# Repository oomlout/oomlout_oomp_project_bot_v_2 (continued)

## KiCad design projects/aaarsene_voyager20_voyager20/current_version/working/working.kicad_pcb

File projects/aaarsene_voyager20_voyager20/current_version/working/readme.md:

# voyager20
 
## summary 
* id: aaarsene_voyager20_voyager20
* user: aaarsene
* name: voyager20
* board: voyager20
* repo: https://github.com/aaarsene/Voyager20
* src_file_repo_kicad_pcb: Voyager20.kicad_pcb
* src_file_repo_kicad_pcb_link: https://github.com/aaarsene/Voyager20/tree/FnRow/Voyager20.kicad_pcb

* src_file_repo_sch: 
* src_file_repo_sch_link: https://github.com/aaarsene/Voyager20/tree/FnRow/
* full details link: https://github.com/oomlout/oomlout_oomp_project_bot_v_2/tree/main/projects/aaarsene_voyager20_voyager20/current_version/working  

## schematic  
  
[schematic (pdf)](working_schematic.pdf) 

## pcb  

[board (pdf)](working.pdf)  

## working_bom
| Id | Designator | Footprint | Quantity | Designation | Supplier and ref |  | None | 
| --- | --- | --- | --- | --- | --- | --- | --- | 
| 1 | MX1,MX2,MX3,MX4,MX5,MX6,MX7,MX8,MX9,MX10,MX11,MX12,MX13,MX14,MX15,MX16,MX17,MX18,MX19,MX20,MX21,MX22,MX23,MX24 | MX-1U | 24 | MX-1U |  |  | [''] | 
| 2 | USB1 | HRO-TYPE-C-31-M-12-Assembly | 1 | HRO-TYPE-C-31-M-12 |  |  | [''] | 
| 3 | MX-E-1,MX-E-2,MX-E-3 | MX-2U-ReversedStabilizers | 3 | MX-2U |  |  | [''] | 
| 4 | G*** | ai-ring-6mm | 1 | LOGO |  |  | [''] | 
| 5 | C1,C2 | C_0603_1608Metric | 2 | 22p |  |  | [''] | 
| 6 | C3 | C_0603_1608Metric | 1 | 1uF |  |  | [''] | 
| 7 | C4,C5,CR1,CR2,CR3,CR4 | C_0603_1608Metric | 6 | 0.1u |  |  | [''] | 
| 8 | C6 | C_0603_1608Metric | 1 | 4.7u |  |  | [''] | 
| 9 | D1,D2,D3,D4,D5,D6,D10,D11,D12,D13,D16,D17,D19,D20,D21,D22,D15,D14,D8,D7,D25,D26,D27,D28 | D_SOD-123 | 24 | SOD-123 |  |  | [''] | 
| 10 | D9,D23,D24,D18 | LED_WS2812B_PLCC4_5.0x5.0mm_P3.2mm | 4 | WS2812B |  |  | [''] | 
| 11 | F1 | Fuse_1206_3216Metric | 1 | 500mA |  |  | [''] | 
| 12 | R1,R5 | R_0805_2012Metric | 2 | 10k |  |  | [''] | 
| 13 | R2,R3 | R_0805_2012Metric | 2 | 22 |  |  | [''] | 
| 14 | R4,R6 | R_0805_2012Metric | 2 | 5.1k |  |  | [''] | 
| 15 | R7,R10,R11,R12,R13,R14,R15,R16,R17,R18,R21,R22,R23,R24,R25,R26,R27,R20,R19,R9,R8,R28,R29,R30,R31 | R_0805_2012Metric | 25 | 1k |  |  | [''] | 
| 16 | SW1 | SKQG-1155865 | 1 | SW_Push |  |  | [''] | 
| 17 | Y1 | Crystal_SMD_3225-4Pin_3.2x2.5mm | 1 | 16MHz |  |  | [''] | 
| 18 | U1 | QFN-32-1EP_5x5mm_P0.5mm_EP3.65x3.65mm | 1 | ATmega32U2-AU |  |  | [''] | 
| 19 | Q1 | SOT-23 | 1 | Q_NPN_BEC |  |  | [''] | 
| 20 | U2 | SOT143B | 1 | PRTR5V0U2X |  |  | [''] | 

## bom_schematic
| Ref | Qnty | Value | Cmp name | Footprint | Description | Vendor | DNP | 
| --- | --- | --- | --- | --- | --- | --- | --- | 
| C1, C2 | 2 | 22p | C_Small | Capacitor_SMD:C_0603_1608Metric | Unpolarized capacitor, small symbol |  |  | 
| C3 | 1 | 1uF | C_Small | Capacitor_SMD:C_0603_1608Metric | Unpolarized capacitor, small symbol |  |  | 
| C4, C5 | 2 | 0.1u | C_Small | Capacitor_SMD:C_0603_1608Metric | Unpolarized capacitor, small symbol |  |  | 
| C6 | 1 | 4.7u | C_Small | Capacitor_SMD:C_0603_1608Metric | Unpolarized capacitor, small symbol |  |  | 
| CR1, CR2, CR3, CR4 | 4 | 0.1u | C_Small | Capacitor_SMD:C_0603_1608Metric | Unpolarized capacitor, small symbol |  |  | 
| D1, D2, D3, D4, D5, D6, D7, D8, D10, D11, D12, D13, D14, D15, D16, D17, D19, D20, D21, D22, D25, D26, D27, D28 | 24 | SOD-123 | D_Small | Diode_SMD:D_SOD-123 | Diode, small symbol |  |  | 
| D9, D18, D23, D24 | 4 | WS2812B | WS2812B | LED_SMD:LED_WS2812B_PLCC4_5.0x5.0mm_P3.2mm | RGB LED with integrated controller |  |  | 
| F1 | 1 | 500mA | Polyfuse_Small | Fuse:Fuse_1206_3216Metric | Resettable fuse, polymeric positive temperature coefficient, small symbol |  |  | 
| MX1, MX2, MX3, MX4, MX5, MX6, MX7, MX8, MX9, MX10, MX11, MX12, MX13, MX14, MX15, MX16, MX17, MX18, MX19, MX20, MX21, MX22, MX23, MX24 | 24 | MX-1U | MX-1U-MX_Alps_Hybrids | MX_Alps_Hybrid:MX-1U |  |  |  | 
| MX-E-1, MX-E-2, MX-E-3 | 3 | MX-2U | MX-1U-MX_Alps_Hybrids | MX_Alps_Hybrid:MX-2U-ReversedStabilizers |  |  |  | 
| Q1 | 1 | Q_NPN_BEC | Q_NPN_BEC | Package_TO_SOT_SMD:SOT-23 | NPN transistor, base/emitter/collector |  |  | 
| R1, R5 | 2 | 10k | R_Small | Resistor_SMD:R_0805_2012Metric | Resistor, small symbol |  |  | 
| R2, R3 | 2 | 22 | R_Small | Resistor_SMD:R_0805_2012Metric | Resistor, small symbol |  |  | 
| R4, R6 | 2 | 5.1k | R_Small | Resistor_SMD:R_0805_2012Metric | Resistor, small symbol |  |  | 
| R7, R8, R9, R10, R11, R12, R13, R14, R15, R16, R17, R18, R19, R20, R21, R22, R23, R24, R25, R26, R27, R28, R29, R30, R31 | 25 | 1k | R_Small | Resistor_SMD:R_0805_2012Metric | Resistor, small symbol |  |  | 
| SW1 | 1 | SW_Push | SW_Push | random-keyboard-parts:SKQG-1155865 | Push button switch, generic, two pins |  |  | 
| U1 | 1 | ATmega32U2-AU | ATmega32U2-AU-MCU_Microchip_ATmega | Package_DFN_QFN:QFN-32-1EP_5x5mm_P0.5mm_EP3.65x3.65mm |  |  |  | 
| U2 | 1 | PRTR5V0U2X | PRTR5V0U2X | random-keyboard-parts:SOT143B |  |  |  | 
| USB1 | 1 | HRO-TYPE-C-31-M-12 | HRO-TYPE-C-31-M-12-Type-C | Type-C:HRO-TYPE-C-31-M-12-Assembly |  |  |  | 
| Y1 | 1 | 16MHz | Crystal_GND24_Small-Device | Crystal:Crystal_SMD_3225-4Pin_3.2x2.5mm |  |  |  |

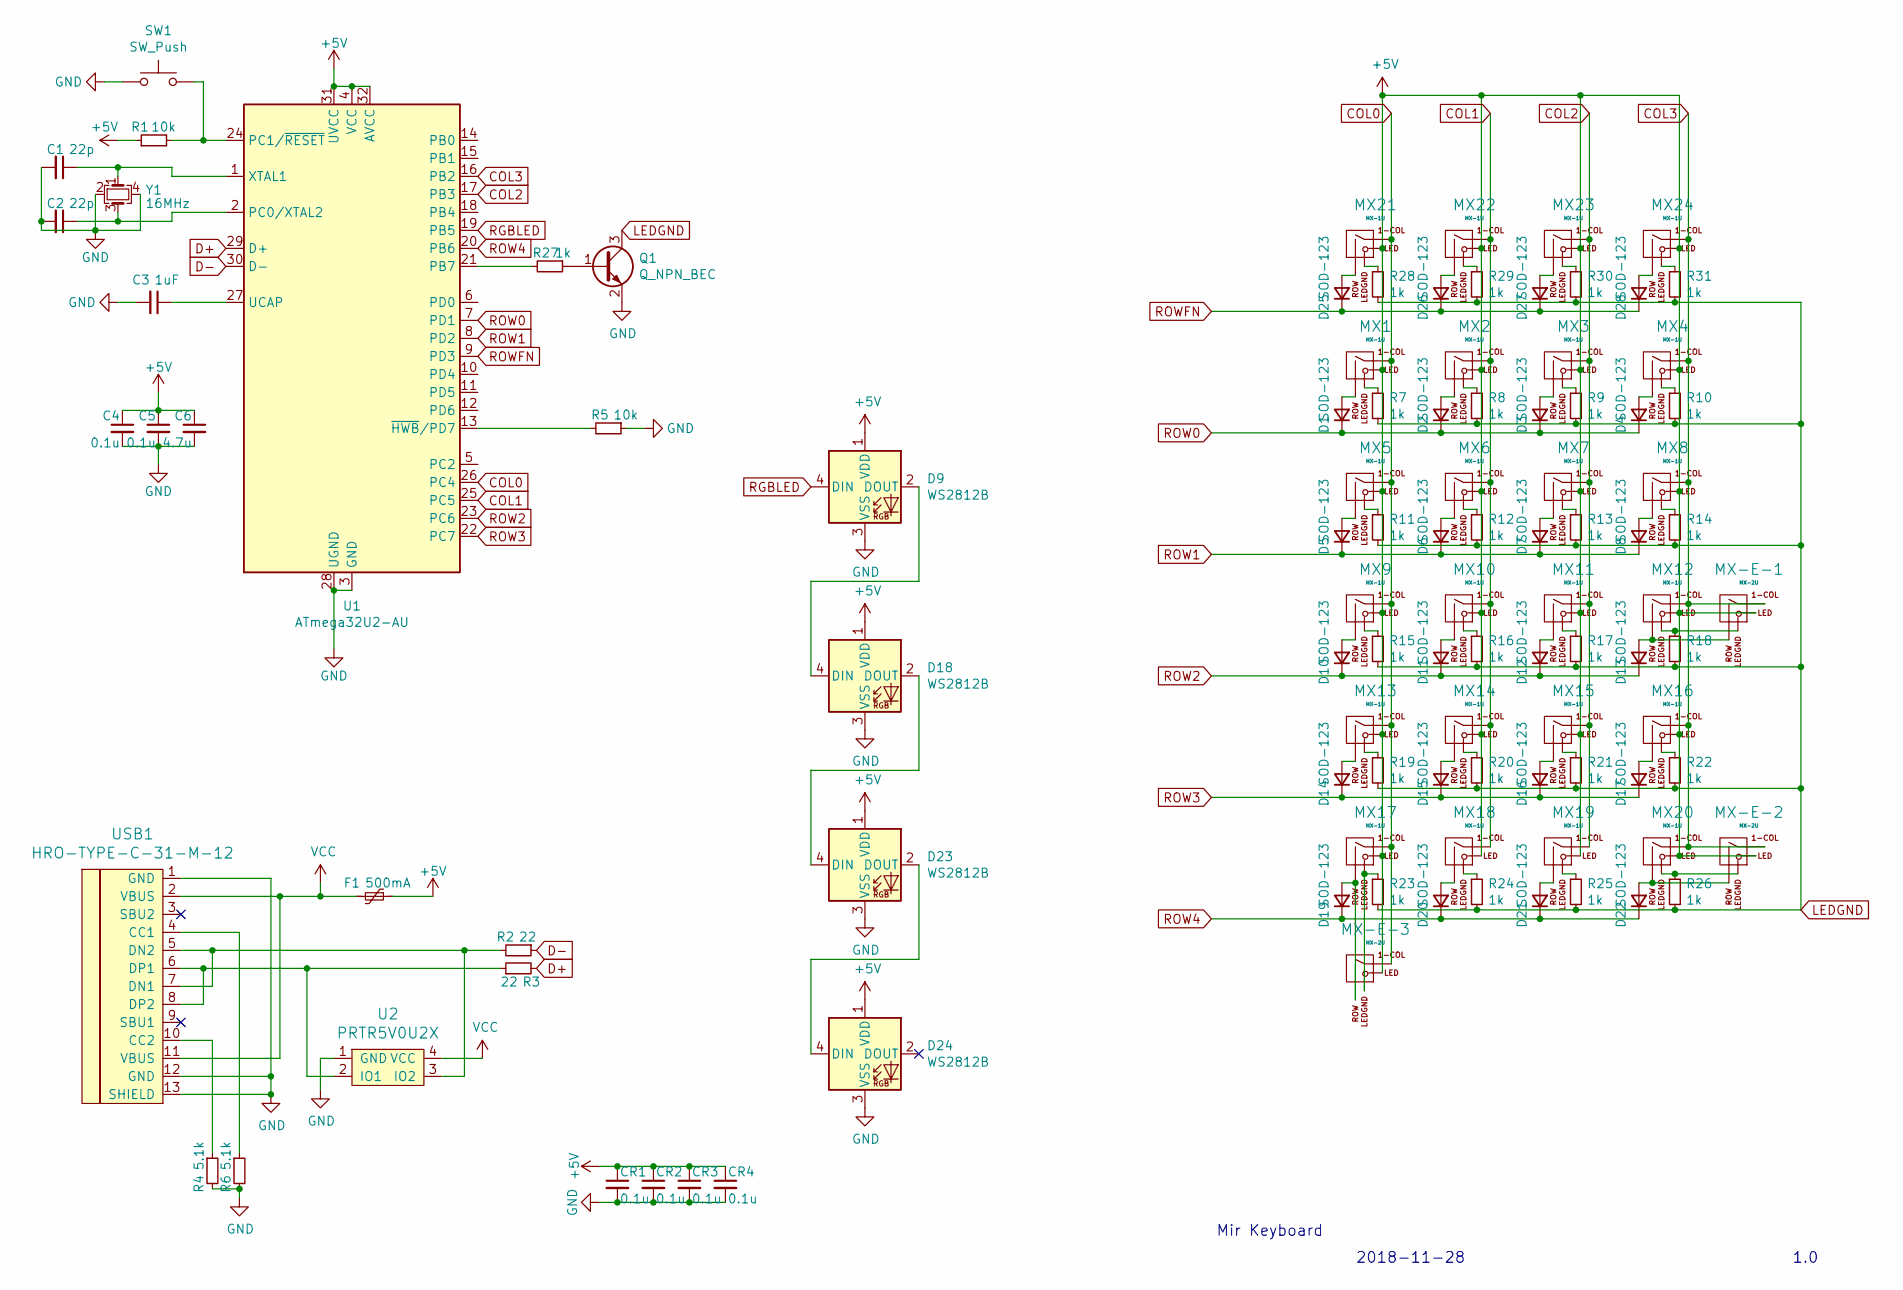
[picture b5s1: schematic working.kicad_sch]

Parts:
C1, C2: 22p; C_0603_1608Metric
C3: 1uF; C_0603_1608Metric
C4, C5: 0.1u; C_0603_1608Metric
C6: 4.7u; C_0603_1608Metric
CR1, CR2, CR3, CR4: 0.1u; C_0603_1608Metric
D1, D2, D3, D4, D5, D6, D7, D8, D10, D11, D12, D13, D14, D15, D16, D17, D19, D20, D21, D22, D25, D26, D27, D28: SOD-123; D_SOD-123
D9, D18, D23, D24: WS2812B; LED_WS2812B_PLCC4_5.0x5.0mm_P3.2mm
F1: 500mA; Fuse_1206_3216Metric
MX1, MX2, MX3, MX4, MX5, MX6, MX7, MX8, MX9, MX10, MX11, MX12, MX13, MX14, MX15, MX16, MX17, MX18, MX19, MX20, MX21, MX22, MX23, MX24: MX-1U
MX-E-1, MX-E-2, MX-E-3: MX-2U; MX-2U-ReversedStabilizers
Q1: Q_NPN_BEC; SOT-23
R1, R5: 10k; R_0805_2012Metric
R2, R3: 22; R_0805_2012Metric
R4, R6: 5.1k; R_0805_2012Metric
R7, R8, R9, R10, R11, R12, R13, R14, R15, R16, R17, R18, R19, R20, R21, R22, R23, R24, R25, R26, R27, R28, R29, R30, R31: 1k; R_0805_2012Metric
SW1: SW_Push; SKQG-1155865
U1: ATmega32U2-AU; QFN-32-1EP_5x5mm_P0.5mm_EP3.65x3.65mm
U2: PRTR5V0U2X; SOT143B
USB1: HRO-TYPE-C-31-M-12; HRO-TYPE-C-31-M-12-Assembly
Y1: 16MHz; Crystal_SMD_3225-4Pin_3.2x2.5mm

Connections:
+5V: C4.1, C5.1, C6.1, CR1.1, CR2.1, CR3.1, CR4.1, D9.1 (VDD), D18.1 (VDD), D23.1 (VDD), D24.1 (VDD), F1.1, MX1.3 (LED), MX2.3 (LED), MX3.3 (LED), MX4.3 (LED), MX5.3 (LED), MX6.3 (LED), MX7.3 (LED), MX8.3 (LED), MX9.3 (LED), MX10.3 (LED), MX11.3 (LED), MX12.3 (LED), MX13.3 (LED), MX14.3 (LED), MX15.3 (LED), MX16.3 (LED), MX17.3 (LED), MX18.3 (LED), MX19.3 (LED), MX20.3 (LED), MX21.3 (LED), MX22.3 (LED), MX23.3 (LED), MX24.3 (LED), MX-E-1.3 (LED), MX-E-2.3 (LED), MX-E-3.3 (LED), R1.1, U1.4 (VCC), U1.31 (UVCC), U1.32 (AVCC)
COL0: MX1.1 (COL), MX5.1 (COL), MX9.1 (COL), MX13.1 (COL), MX17.1 (COL), MX21.1 (COL), MX-E-3.1 (COL), U1.26 (PC4)
COL1: MX2.1 (COL), MX6.1 (COL), MX10.1 (COL), MX14.1 (COL), MX18.1 (COL), MX22.1 (COL), U1.25 (PC5)
COL2: MX3.1 (COL), MX7.1 (COL), MX11.1 (COL), MX15.1 (COL), MX19.1 (COL), MX23.1 (COL), U1.17 (PB3)
COL3: MX4.1 (COL), MX8.1 (COL), MX12.1 (COL), MX16.1 (COL), MX20.1 (COL), MX24.1 (COL), MX-E-1.1 (COL), MX-E-2.1 (COL), U1.16 (PB2)
D+: R3.2, U1.29 (D+)
D-: R2.1, U1.30 (D-)
GND: C1.2, C2.2, C3.2, C4.2, C5.2, C6.2, CR1.2, CR2.2, CR3.2, CR4.2, D9.3 (VSS), D18.3 (VSS), D23.3 (VSS), D24.3 (VSS), Q1.2 (E), R4.2, R5.1, R6.2, SW1.1, U1.3 (GND), U1.28 (UGND), U2.1 (GND), USB1.1 (GND), USB1.12 (GND), USB1.13 (SHIELD), Y1.2, Y1.4
LEDGND: Q1.3 (C), R7.2, R8.2, R9.2, R10.2, R11.2, R12.2, R13.2, R14.2, R15.2, R16.2, R17.2, R18.2, R19.2, R20.2, R21.2, R22.2, R23.2, R24.2, R25.2, R26.2, R28.2, R29.2, R30.2, R31.2
unnamed: C1.1, U1.1 (XTAL1), Y1.1
unnamed: C2.1, U1.2 (PC0/XTAL2), Y1.3
unnamed: C3.1, U1.27 (UCAP)
unnamed: D1.2 (A), MX1.2 (ROW)
unnamed: D2.2 (A), MX2.2 (ROW)
unnamed: D3.2 (A), MX3.2 (ROW)
unnamed: D4.2 (A), MX4.2 (ROW)
unnamed: D5.2 (A), MX5.2 (ROW)
unnamed: D6.2 (A), MX6.2 (ROW)
unnamed: D7.2 (A), MX7.2 (ROW)
unnamed: D8.2 (A), MX8.2 (ROW)
unnamed: D10.2 (A), MX9.2 (ROW)
unnamed: D11.2 (A), MX10.2 (ROW)
unnamed: D12.2 (A), MX11.2 (ROW)
unnamed: D13.2 (A), MX12.2 (ROW), MX-E-1.2 (ROW)
unnamed: D14.2 (A), MX13.2 (ROW)
unnamed: D15.2 (A), MX14.2 (ROW)
unnamed: D16.2 (A), MX15.2 (ROW)
unnamed: D17.2 (A), MX16.2 (ROW)
unnamed: D18.2 (DOUT), D23.4 (DIN)
unnamed: D9.2 (DOUT), D18.4 (DIN)
unnamed: D19.2 (A), MX17.2 (ROW), MX-E-3.2 (ROW)
unnamed: D20.2 (A), MX18.2 (ROW)
unnamed: D21.2 (A), MX19.2 (ROW)
unnamed: D22.2 (A), MX20.2 (ROW), MX-E-2.2 (ROW)
unnamed: D23.2 (DOUT), D24.4 (DIN)
unnamed: D25.2 (A), MX21.2 (ROW)
unnamed: D26.2 (A), MX22.2 (ROW)
unnamed: D27.2 (A), MX23.2 (ROW)
unnamed: D28.2 (A), MX24.2 (ROW)
unnamed: MX1.4 (LEDGND), R7.1
unnamed: MX2.4 (LEDGND), R8.1
unnamed: MX3.4 (LEDGND), R9.1
unnamed: MX4.4 (LEDGND), R10.1
unnamed: MX5.4 (LEDGND), R11.1
unnamed: MX6.4 (LEDGND), R12.1
unnamed: MX7.4 (LEDGND), R13.1
unnamed: MX8.4 (LEDGND), R14.1
unnamed: MX9.4 (LEDGND), R15.1
unnamed: MX10.4 (LEDGND), R16.1
unnamed: MX11.4 (LEDGND), R17.1
unnamed: MX13.4 (LEDGND), R19.1
unnamed: MX14.4 (LEDGND), R20.1
unnamed: MX15.4 (LEDGND), R21.1
unnamed: MX16.4 (LEDGND), R22.1
unnamed: MX18.4 (LEDGND), R24.1
unnamed: MX19.4 (LEDGND), R25.1
unnamed: MX21.4 (LEDGND), R28.1
unnamed: MX22.4 (LEDGND), R29.1
unnamed: MX23.4 (LEDGND), R30.1
unnamed: MX24.4 (LEDGND), R31.1
unnamed: MX12.4 (LEDGND), MX-E-1.4 (LEDGND), R18.1
unnamed: MX20.4 (LEDGND), MX-E-2.4 (LEDGND), R26.1
unnamed: MX17.4 (LEDGND), MX-E-3.4 (LEDGND), R23.1
unnamed: Q1.1 (B), R27.1
unnamed: R1.2, SW1.2, U1.24 (PC1/~RESET)
unnamed: R2.2, U2.3 (IO2), USB1.5 (DN2), USB1.7 (DN1)
unnamed: R3.1, U2.2 (IO1), USB1.6 (DP1), USB1.8 (DP2)
unnamed: R4.1, USB1.10 (CC2)
unnamed: R5.2, U1.13 (~HWB/PD7)
unnamed: R6.1, USB1.4 (CC1)
unnamed: R27.2, U1.21 (PB7)
RGBLED: D9.4 (DIN), U1.19 (PB5)
ROW0: D1.1 (K), D2.1 (K), D3.1 (K), D4.1 (K), U1.7 (PD1)
ROW1: D5.1 (K), D6.1 (K), D7.1 (K), D8.1 (K), U1.8 (PD2)
ROW2: D10.1 (K), D11.1 (K), D12.1 (K), D13.1 (K), U1.23 (PC6)
ROW3: D14.1 (K), D15.1 (K), D16.1 (K), D17.1 (K), U1.22 (PC7)
ROW4: D19.1 (K), D20.1 (K), D21.1 (K), D22.1 (K), U1.20 (PB6)
ROWFN: D25.1 (K), D26.1 (K), D27.1 (K), D28.1 (K), U1.9 (PD3)
VCC: F1.2, U2.4 (VCC), USB1.2 (VBUS), USB1.11 (VBUS)

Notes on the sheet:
2018-11-28
Mir Keyboard
1.0

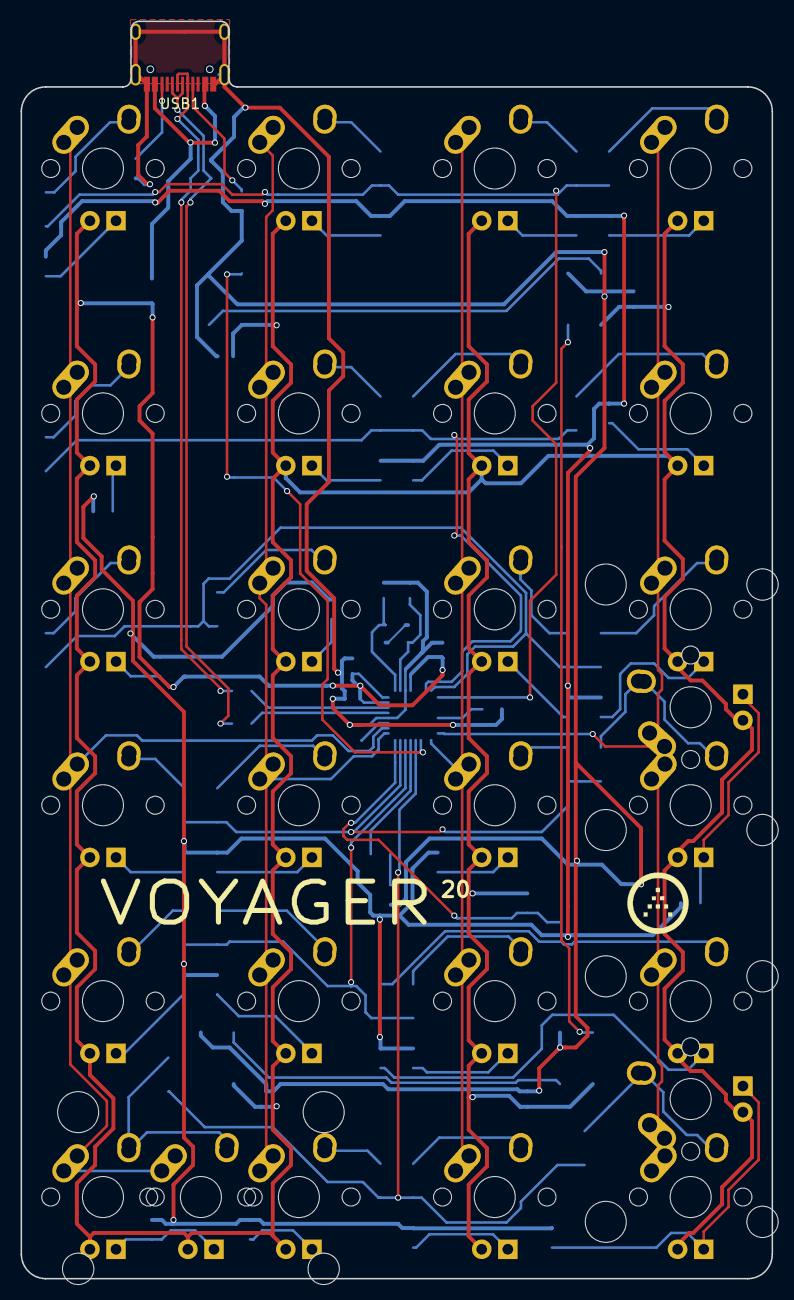
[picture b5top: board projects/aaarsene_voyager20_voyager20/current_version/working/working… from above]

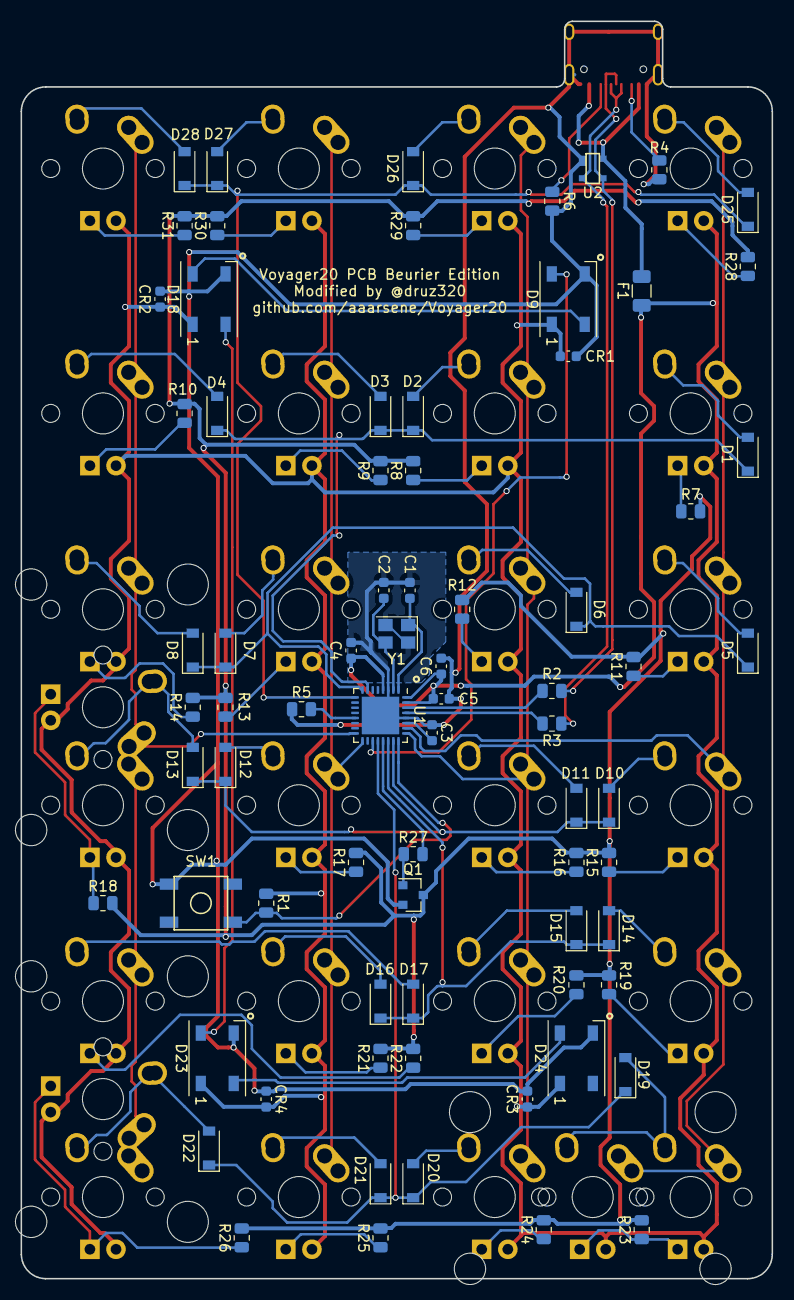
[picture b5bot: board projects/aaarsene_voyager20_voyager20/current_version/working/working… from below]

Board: 2 copper layers, 73.0 x 122.3 mm, 103 parts (75 on the bottom side), 79 nets.

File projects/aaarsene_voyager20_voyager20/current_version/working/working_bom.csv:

"Id";"Designator";"Footprint";"Quantity";"Designation";"Supplier and ref";
1;"MX1,MX2,MX3,MX4,MX5,MX6,MX7,MX8,MX9,MX10,MX11,MX12,MX13,MX14,MX15,MX16,MX17,MX18,MX19,MX20,MX21,MX22,MX23,MX24";"MX-1U";24;"MX-1U";;;
2;"USB1";"HRO-TYPE-C-31-M-12-Assembly";1;"HRO-TYPE-C-31-M-12";;;
3;"MX-E-1,MX-E-2,MX-E-3";"MX-2U-ReversedStabilizers";3;"MX-2U";;;
4;"G***";"ai-ring-6mm";1;"LOGO";;;
5;"C1,C2";"C_0603_1608Metric";2;"22p";;;
6;"C3";"C_0603_1608Metric";1;"1uF";;;
7;"C4,C5,CR1,CR2,CR3,CR4";"C_0603_1608Metric";6;"0.1u";;;
8;"C6";"C_0603_1608Metric";1;"4.7u";;;
9;"D1,D2,D3,D4,D5,D6,D10,D11,D12,D13,D16,D17,D19,D20,D21,D22,D15,D14,D8,D7,D25,D26,D27,D28";"D_SOD-123";24;"SOD-123";;;
10;"D9,D23,D24,D18";"LED_WS2812B_PLCC4_5.0x5.0mm_P3.2mm";4;"WS2812B";;;
11;"F1";"Fuse_1206_3216Metric";1;"500mA";;;
12;"R1,R5";"R_0805_2012Metric";2;"10k";;;
13;"R2,R3";"R_0805_2012Metric";2;"22";;;
14;"R4,R6";"R_0805_2012Metric";2;"5.1k";;;
15;"R7,R10,R11,R12,R13,R14,R15,R16,R17,R18,R21,R22,R23,R24,R25,R26,R27,R20,R19,R9,R8,R28,R29,R30,R31";"R_0805_2012Metric";25;"1k";;;
16;"SW1";"SKQG-1155865";1;"SW_Push";;;
17;"Y1";"Crystal_SMD_3225-4Pin_3.2x2.5mm";1;"16MHz";;;
18;"U1";"QFN-32-1EP_5x5mm_P0.5mm_EP3.65x3.65mm";1;"ATmega32U2-AU";;;
19;"Q1";"SOT-23";1;"Q_NPN_BEC";;;
20;"U2";"SOT143B";1;"PRTR5V0U2X";;;

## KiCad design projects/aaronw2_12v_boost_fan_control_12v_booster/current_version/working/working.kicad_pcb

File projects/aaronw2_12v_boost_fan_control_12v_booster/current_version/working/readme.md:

# 12v_boost_fan_control
 
## summary 
* id: aaronw2_12v_boost_fan_control_12v_booster
* user: aaronw2
* name: 12v_boost_fan_control
* board: 12v_booster
* repo: https://github.com/aaronw2/12v-Boost-Fan-Control
* src_file_repo_kicad_pcb: 12v-booster.kicad_pcb
* src_file_repo_kicad_pcb_link: https://github.com/aaronw2/12v-Boost-Fan-Control/tree/master/12v-booster.kicad_pcb

* src_file_repo_sch: 12v-booster.sch
* src_file_repo_sch_link: https://github.com/aaronw2/12v-Boost-Fan-Control/tree/master/12v-booster.sch
* full details link: https://github.com/oomlout/oomlout_oomp_project_bot_v_2/tree/main/projects/aaronw2_12v_boost_fan_control_12v_booster/current_version/working  

## schematic  
  
[schematic (pdf)](working_schematic.pdf) 

## pcb  

[board (pdf)](working.pdf)  

## working_bom
| Id | Designator | Footprint | Quantity | Designation | Supplier and ref |  | None | 
| --- | --- | --- | --- | --- | --- | --- | --- | 
| 1 | R1 | R_0603_1608Metric | 1 | 86.6k |  |  | [''] | 
| 2 | R2 | R_0603_1608Metric | 1 | 18.2k |  |  | [''] | 
| 3 | R3 | R_0603_1608Metric | 1 | 1.69k |  |  | [''] | 
| 4 | R4 | R_0603_1608Metric | 1 | 10k |  |  | [''] | 
| 5 | C3 | C_1210_3225Metric | 1 | 22uF |  |  | [''] | 
| 6 | C1 | C_0603_1608Metric | 1 | 6.8uF |  |  | [''] | 
| 7 | C2 | C_0603_1608Metric | 1 | 100nF |  |  | [''] | 
| 8 | C5 | C_0603_1608Metric | 1 | 22nF |  |  | [''] | 
| 9 | C6 | C_0603_1608Metric | 1 | 820pF |  |  | [''] | 
| 10 | C7 | C_0603_1608Metric | 1 | 47nF |  |  | [''] | 
| 11 | R5 | R_0603_1608Metric | 1 | 100k |  |  | [''] | 
| 12 | Q1 | SOT-323_SC-70 | 1 | BSS214NW |  |  | [''] | 
| 13 | U1 | QFN-16-1EP_3x3mm_P0.5mm_EP2.7x2.7mm_ThermalVias | 1 | TPS55340-Q1 |  |  | [''] | 
| 14 | D1 | D_SOD-123F | 1 | D_Schottky |  |  | [''] | 
| 15 | C4 | C_0603_1608Metric | 1 | 1uF |  |  | [''] | 
| 16 | J1 | PinHeader_1x04_P2.54mm_Horizontal | 1 | Conn_01x04 |  |  | [''] | 
| 17 | J2 | PinHeader_1x03_P2.54mm_Horizontal | 1 | Conn_01x03 |  |  | [''] | 
| 18 | L1 | L_Vishay_IHLP-1212 | 1 | 3.3uH |  |  | [''] | 

## bom_schematic
| Ref | Qnty | Value | Cmp name | Footprint | Description | Vendor | DNP | 
| --- | --- | --- | --- | --- | --- | --- | --- | 
| C1 | 1 | 6.8uF | C | Capacitor_SMD:C_0603_1608Metric | Unpolarized capacitor |  |  | 
| C2 | 1 | 100nF | C | Capacitor_SMD:C_0603_1608Metric | Unpolarized capacitor |  |  | 
| C3 | 1 | 22uF | C | Capacitor_SMD:C_1210_3225Metric | Unpolarized capacitor |  |  | 
| C4 | 1 | 1uF | C | Capacitor_SMD:C_0603_1608Metric | Unpolarized capacitor |  |  | 
| C5 | 1 | 22nF | C | Capacitor_SMD:C_0603_1608Metric | Unpolarized capacitor |  |  | 
| C6 | 1 | 820pF | C | Capacitor_SMD:C_0603_1608Metric | Unpolarized capacitor |  |  | 
| C7 | 1 | 47nF | C | Capacitor_SMD:C_0603_1608Metric | Unpolarized capacitor |  |  | 
| D1 | 1 | D_Schottky | D_Schottky | Diode_SMD:D_SOD-123F | Schottky diode |  |  | 
| J1 | 1 | Conn_01x04 | Conn_01x04 | Connector_PinHeader_2.54mm:PinHeader_1x04_P2.54mm_Horizontal | Generic connector, single row, 01x04, script generated (kicad-library-utils/schlib/autogen/connector/) |  |  | 
| J2 | 1 | Conn_01x03 | Conn_01x03 | Connector_PinHeader_2.54mm:PinHeader_1x03_P2.54mm_Horizontal | Generic connector, single row, 01x03, script generated (kicad-library-utils/schlib/autogen/connector/) |  |  | 
| L1 | 1 | 3.3uH | L | Aaron:L_Vishay_IHLP-1212 | Inductor |  |  | 
| Q1 | 1 | BSS214NW | BSS214NW | Package_TO_SOT_SMD:SOT-323_SC-70 | 20V Vds, 1.5A Id, N-Channel MOSFET, SOT-323 |  |  | 
| R1 | 1 | 86.6k | R | Resistor_SMD:R_0603_1608Metric | Resistor |  |  | 
| R2 | 1 | 18.2k | R | Resistor_SMD:R_0603_1608Metric | Resistor |  |  | 
| R3 | 1 | 1.69k | R | Resistor_SMD:R_0603_1608Metric | Resistor |  |  | 
| R4 | 1 | 10k | R | Resistor_SMD:R_0603_1608Metric | Resistor |  |  | 
| R5 | 1 | 100k | R | Resistor_SMD:R_0603_1608Metric | Resistor |  |  | 
| U1 | 1 | TPS55340-Q1 | TPS55340-Q1-texas | Aaron:QFN-16-1EP_3x3mm_P0.5mm_EP2.7x2.7mm_ThermalVias |  |  |  |

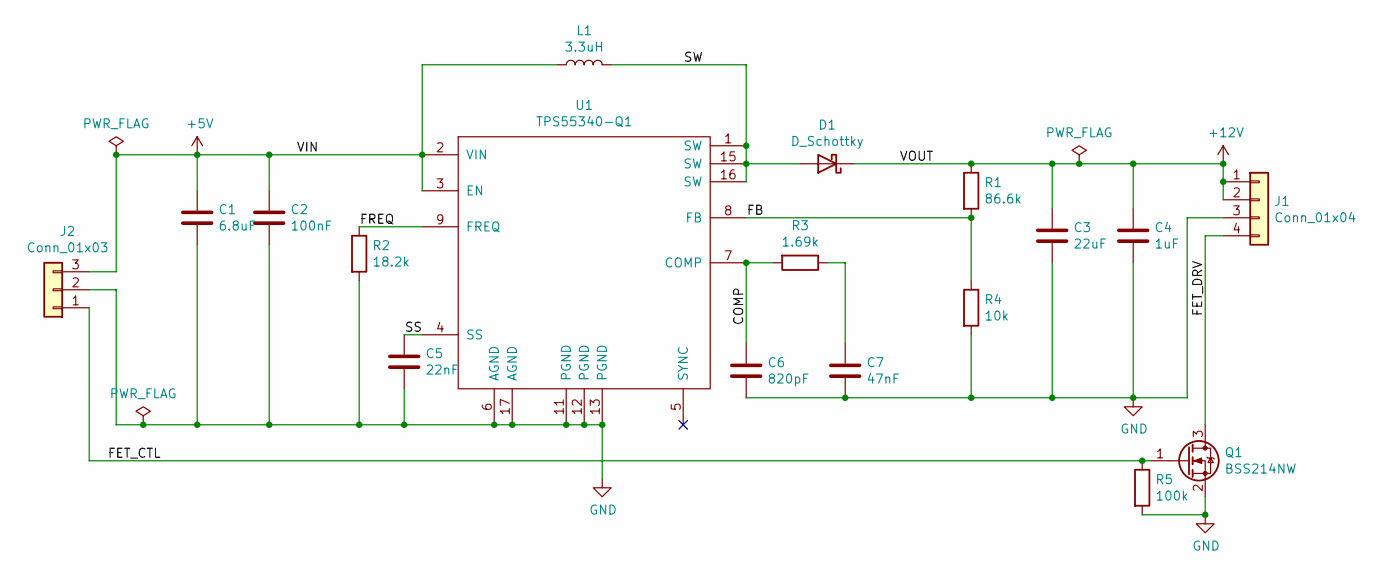
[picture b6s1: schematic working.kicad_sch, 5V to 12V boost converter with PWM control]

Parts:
C1: 6.8uF; C_0603_1608Metric; MPN C1608X5R1E685K080AC
C2: 100nF; C_0603_1608Metric; MPN CL10B104KO8WPNC
C3: 22uF; C_1210_3225Metric; MPN CL32B226MOJNNNE
C4: 1uF; C_0603_1608Metric; MPN CL10B105KP8NNNC
C5: 22nF; C_0603_1608Metric; MPN CL10B223KB8WPNC
C6: 820pF; C_0603_1608Metric; MPN C0603C821J5RACTU
C7: 47nF; C_0603_1608Metric; MPN GRM188R61H474KA12D
D1: D_Schottky; D_SOD-123F; MPN SS24FL
J1: Conn_01x04; PinHeader_1x04_P2.54mm_Horizontal
J2: Conn_01x03; PinHeader_1x03_P2.54mm_Horizontal
L1: 3.3uH; L_Vishay_IHLP-1212; MPN IHLP1212BZER3R3M11
Q1: BSS214NW; SOT-323_SC-70; MPN BSS214NWH6327XTSA1
R1: 86.6k; R_0603_1608Metric; MPN CRCW060386K6FKEA
R2: 18.2k; R_0603_1608Metric; MPN CRCW060318K2FKEA
R3: 1.69k; R_0603_1608Metric; MPN CRCW06031K69FKEA
R4: 10k; R_0603_1608Metric; MPN CRCW060310K0FKEC
R5: 100k; R_0603_1608Metric; MPN CRG0603F100K
U1: TPS55340-Q1; QFN-16-1EP_3x3mm_P0.5mm_EP2.7x2.7mm_ThermalVias; MPN TPS55340RTER

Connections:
+5V: C1.1, C2.1, J2.3, L1.1, U1.2 (VIN), U1.3 (EN)
+12V: C3.1, C4.1, D1.1 (K), J1.1, J1.2, R1.1
/COMP: C6.1, R3.2, U1.7 (COMP)
/FB: R1.2, R4.1, U1.8 (FB)
/FET_CTL: J2.1, Q1.1 (G), R5.1
/FET_DRV: J1.4, Q1.3 (D)
/FREQ: R2.1, U1.9 (FREQ)
/SS: C5.1, U1.4 (SS)
/SW: D1.2 (A), L1.2, U1.1 (SW), U1.15 (SW), U1.16 (SW)
GND: C1.2, C2.2, C3.2, C4.2, C5.2, C6.2, C7.2, J1.3, J2.2, Q1.2 (S), R2.2, R4.2, R5.2, U1.6 (AGND), U1.11 (PGND), U1.12 (PGND), U1.13 (PGND), U1.17 (AGND)
unnamed: C7.1, R3.1

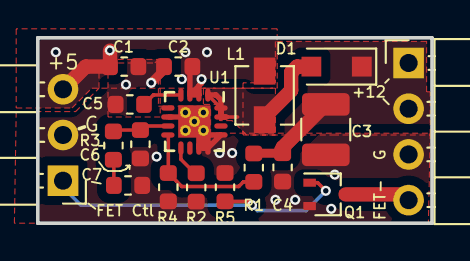
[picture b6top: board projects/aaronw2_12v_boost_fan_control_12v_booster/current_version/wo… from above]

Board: 2 copper layers, 21.9 x 10.3 mm, 18 parts (0 on the bottom side), 11 nets.

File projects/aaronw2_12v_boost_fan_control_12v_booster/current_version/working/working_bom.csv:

"Id";"Designator";"Footprint";"Quantity";"Designation";"Supplier and ref";
1;"R1";"R_0603_1608Metric";1;"86.6k";;;
2;"R2";"R_0603_1608Metric";1;"18.2k";;;
3;"R3";"R_0603_1608Metric";1;"1.69k";;;
4;"R4";"R_0603_1608Metric";1;"10k";;;
5;"C3";"C_1210_3225Metric";1;"22uF";;;
6;"C1";"C_0603_1608Metric";1;"6.8uF";;;
7;"C2";"C_0603_1608Metric";1;"100nF";;;
8;"C5";"C_0603_1608Metric";1;"22nF";;;
9;"C6";"C_0603_1608Metric";1;"820pF";;;
10;"C7";"C_0603_1608Metric";1;"47nF";;;
11;"R5";"R_0603_1608Metric";1;"100k";;;
12;"Q1";"SOT-323_SC-70";1;"BSS214NW";;;
13;"U1";"QFN-16-1EP_3x3mm_P0.5mm_EP2.7x2.7mm_ThermalVias";1;"TPS55340-Q1";;;
14;"D1";"D_SOD-123F";1;"D_Schottky";;;
15;"C4";"C_0603_1608Metric";1;"1uF";;;
16;"J1";"PinHeader_1x04_P2.54mm_Horizontal";1;"Conn_01x04";;;
17;"J2";"PinHeader_1x03_P2.54mm_Horizontal";1;"Conn_01x03";;;
18;"L1";"L_Vishay_IHLP-1212";1;"3.3uH";;;

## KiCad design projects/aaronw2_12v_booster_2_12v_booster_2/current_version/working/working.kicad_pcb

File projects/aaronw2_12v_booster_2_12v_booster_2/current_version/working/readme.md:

# 12v_booster_2
 
## summary 
* id: aaronw2_12v_booster_2_12v_booster_2
* user: aaronw2
* name: 12v_booster_2
* board: 12v_booster_2
* repo: https://github.com/aaronw2/12v-booster-2
* src_file_repo_kicad_pcb: 12v-booster-2.kicad_pcb
* src_file_repo_kicad_pcb_link: https://github.com/aaronw2/12v-booster-2/tree/master/12v-booster-2.kicad_pcb

* src_file_repo_sch: 12v-booster-2.sch
* src_file_repo_sch_link: https://github.com/aaronw2/12v-booster-2/tree/master/12v-booster-2.sch
* full details link: https://github.com/oomlout/oomlout_oomp_project_bot_v_2/tree/main/projects/aaronw2_12v_booster_2_12v_booster_2/current_version/working  

## schematic  
  
[schematic (pdf)](working_schematic.pdf) 

## pcb  

[board (pdf)](working.pdf)  

## working_bom
| Id | Designator | Footprint | Quantity | Designation | Supplier and ref |  | None | 
| --- | --- | --- | --- | --- | --- | --- | --- | 
| 1 | R4 | R_0603_1608Metric | 1 | 44.2K |  |  | [''] | 
| 2 | R3 | R_0603_1608Metric | 1 | 68.1K |  |  | [''] | 
| 3 | R2 | R_0603_1608Metric | 1 | 88.7K |  |  | [''] | 
| 4 | R1 | R_0603_1608Metric | 1 | 100K |  |  | [''] | 
| 5 | Q1 | SOT-323_SC-70 | 1 | BSS214NW |  |  | [''] | 
| 6 | C1,C10 | C_1206_3216Metric | 2 | 68uF |  |  | [''] | 
| 7 | C9,C7,C8 | C_0805_2012Metric | 3 | 22uF |  |  | [''] | 
| 8 | C4 | C_0603_1608Metric | 1 | 0.1uF |  |  | [''] | 
| 9 | C3 | C_0603_1608Metric | 1 | 680pF |  |  | [''] | 
| 10 | C2 | C_0603_1608Metric | 1 | 4.7uF |  |  | [''] | 
| 11 | Q2 | SOIC127P600X175-8N | 1 | Si4421DY |  |  | [''] | 
| 12 | L1 | L_Vishay_IHLP-2020 | 1 | 0.068uH |  |  | [''] | 
| 13 | R7 | R_0603_1608Metric | 1 | 80.6K |  |  | [''] | 
| 14 | R6 | R_0603_1608Metric | 1 | 732K |  |  | [''] | 
| 15 | J1,J2 | PinHeader_1x06_P2.54mm_Vertical | 2 | Conn_01x06 |  |  | [''] | 
| 16 | C5 | C_0603_1608Metric | 1 | 0.018uF |  |  | [''] | 
| 17 | R5 | R_0603_1608Metric | 1 | 162K |  |  | [''] | 
| 18 | C6 | C_0603_1608Metric | 1 | 3.3uF |  |  | [''] | 
| 19 | U1 | Texas_13_3.0x3.5mm_VQFN_Hotrod_Pitch_0.5mm | 1 | TPS611781RNW |  |  | [''] | 

## bom_schematic
| Ref | Qnty | Value | Cmp name | Footprint | Description | Vendor | DNP | 
| --- | --- | --- | --- | --- | --- | --- | --- | 
| C1, C10 | 2 | 68uF | C | Capacitor_SMD:C_1206_3216Metric | Unpolarized capacitor |  |  | 
| C2 | 1 | 4.7uF | C | Capacitor_SMD:C_0603_1608Metric | Unpolarized capacitor |  |  | 
| C3 | 1 | 680pF | C | Capacitor_SMD:C_0603_1608Metric | Unpolarized capacitor |  |  | 
| C4 | 1 | 0.1uF | C | Capacitor_SMD:C_0603_1608Metric | Unpolarized capacitor |  |  | 
| C5 | 1 | 0.018uF | C | Capacitor_SMD:C_0603_1608Metric | Unpolarized capacitor |  |  | 
| C6 | 1 | 3.3uF | C | Capacitor_SMD:C_0603_1608Metric | Unpolarized capacitor |  |  | 
| C7, C8, C9 | 3 | 22uF | C | Capacitor_SMD:C_0805_2012Metric | Unpolarized capacitor |  |  | 
| J1, J2 | 2 | Conn_01x06 | Conn_01x06 | Connector_PinHeader_2.54mm:PinHeader_1x06_P2.54mm_Vertical | Generic connector, single row, 01x06, script generated (kicad-library-utils/schlib/autogen/connector/) |  |  | 
| L1 | 1 | 0.068uH | L | Inductor_SMD:L_Vishay_IHLP-2020 | Inductor |  |  | 
| Q1 | 1 | BSS214NW | BSS214NW | Package_TO_SOT_SMD:SOT-323_SC-70 | 20V Vds, 1.5A Id, N-Channel MOSFET, SOT-323 |  |  | 
| Q2 | 1 | Si4421DY | Si4421DY-Aaron | Aaron:SOIC127P600X175-8N |  |  |  | 
| R1 | 1 | 100K | R | Resistor_SMD:R_0603_1608Metric | Resistor |  |  | 
| R2 | 1 | 88.7K | R | Resistor_SMD:R_0603_1608Metric | Resistor |  |  | 
| R3 | 1 | 68.1K | R | Resistor_SMD:R_0603_1608Metric | Resistor |  |  | 
| R4 | 1 | 44.2K | R | Resistor_SMD:R_0603_1608Metric | Resistor |  |  | 
| R5 | 1 | 162K | R | Resistor_SMD:R_0603_1608Metric | Resistor |  |  | 
| R6 | 1 | 732K | R | Resistor_SMD:R_0603_1608Metric | Resistor |  |  | 
| R7 | 1 | 80.6K | R | Resistor_SMD:R_0603_1608Metric | Resistor |  |  | 
| U1 | 1 | TPS611781RNW | TPS611781RNW-Aaron | Aaron:Texas_13_3.0x3.5mm_VQFN_Hotrod_Pitch_0.5mm |  |  |  |

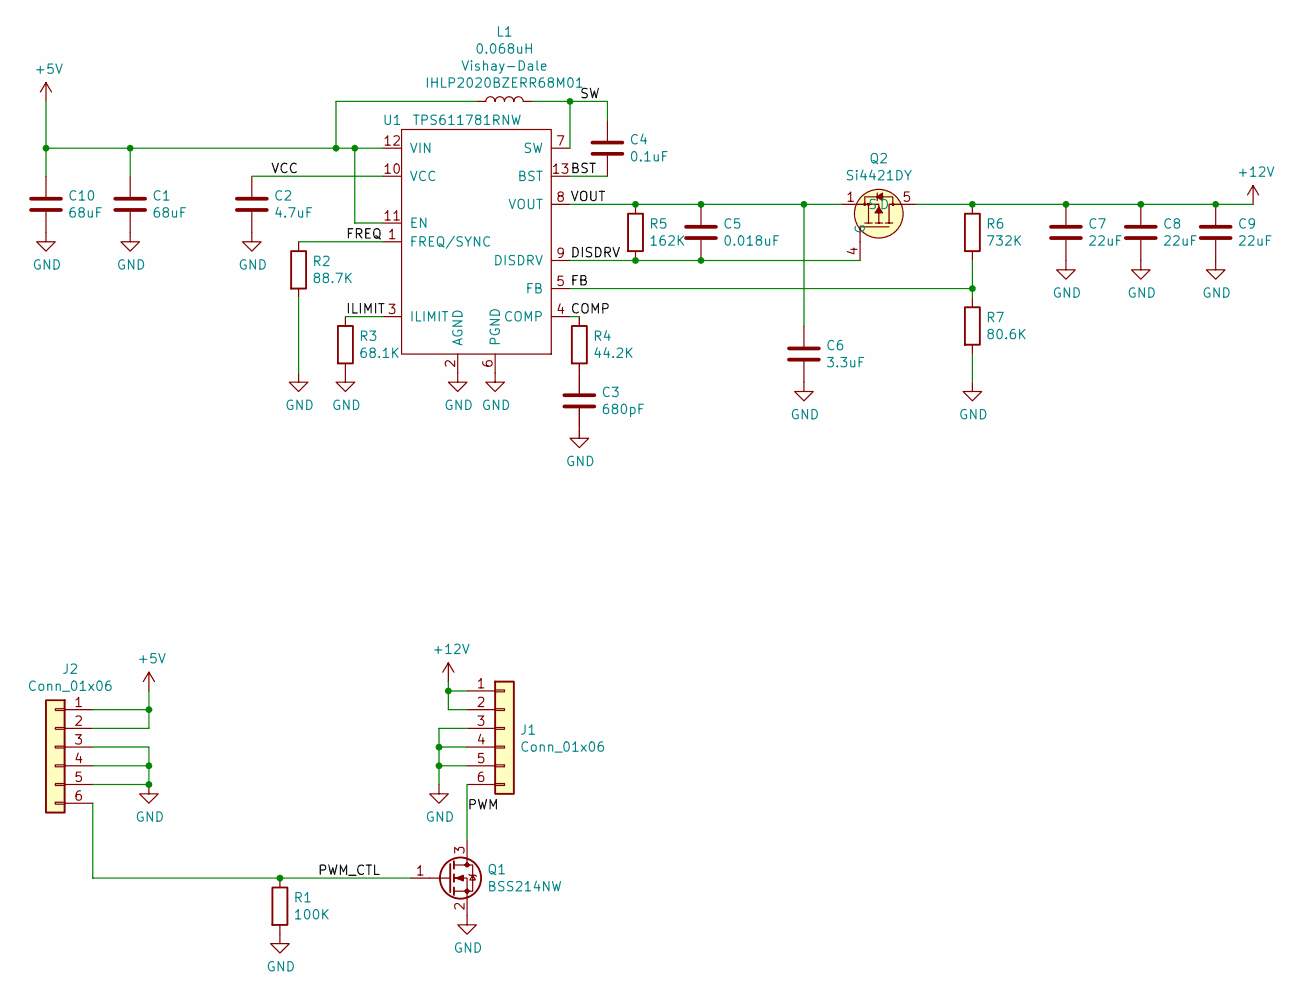
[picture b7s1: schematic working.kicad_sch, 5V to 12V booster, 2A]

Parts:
C1, C10: 68uF; C_1206_3216Metric; MPN C3216X5R1A686M160AC
C2: 4.7uF; C_0603_1608Metric; MPN C1608X5R1E475K080AC
C3: 680pF; C_0603_1608Metric; MPN 885012206107
C4: 0.1uF; C_0603_1608Metric; MPN CL10B104KO8WPNC
C5: 0.018uF; C_0603_1608Metric; MPN C0603C183J3RAC7867
C6: 3.3uF; C_0603_1608Metric; MPN C1608X5R1V335K080AC
C7, C8, C9: 22uF; C_0805_2012Metric; MPN C2012X5R1V226M125AC
J1, J2: Conn_01x06; PinHeader_1x06_P2.54mm_Vertical
L1: 0.068uH; L_Vishay_IHLP-2020; MPN IHLP2020BZERR68M01
Q1: BSS214NW; SOT-323_SC-70; MPN BSS214NWH6327XTSA1
Q2: Si4421DY; SOIC127P600X175-8N; MPN SI4421DY-T1-E3
R1: 100K; R_0603_1608Metric; MPN RC0603JR-07100KL
R2: 88.7K; R_0603_1608Metric; MPN RC0603FR-0788K7L
R3: 68.1K; R_0603_1608Metric; MPN RC0603FR-0768K1L
R4: 44.2K; R_0603_1608Metric; MPN RC0603FR-0744K2L
R5: 162K; R_0603_1608Metric; MPN TNPW0603162KBEEA
R6: 732K; R_0603_1608Metric; MPN RC0603FR-07732KL
R7: 80.6K; R_0603_1608Metric; MPN CRCW060380K6FKEA
U1: TPS611781RNW; Texas_13_3.0x3.5mm_VQFN_Hotrod_Pitch_0.5mm; MPN TPS611781RNWR

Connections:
+5V: C1.1, C10.1, J2.1, J2.2, L1.1, U1.11 (EN), U1.12 (VIN)
+12V: C7.1, C8.1, C9.1, J1.1, J1.2, Q2.5 (D), Q2.6 (D), Q2.7 (D), Q2.8 (D), R6.1
/BST: C4.2, U1.13 (BST)
/COMP: R4.1, U1.4 (COMP)
/DISDRV: C5.2, Q2.4 (G), R5.2, U1.9 (DISDRV)
/FB: R6.2, R7.1, U1.5 (FB)
/FREQ: R2.1, U1.1 (FREQ/SYNC)
/ILIMIT: R3.1, U1.3 (ILIMIT)
/PWM: J1.6, Q1.3 (D)
/PWM_CTL: J2.6, Q1.1 (G), R1.1
/SW: C4.1, L1.2, U1.7 (SW)
/VCC: C2.1, U1.10 (VCC)
/VOUT: C5.1, C6.1, Q2.1 (S), Q2.2 (S), Q2.3 (S), R5.1, U1.8 (VOUT)
GND: C1.2, C2.2, C3.2, C6.2, C7.2, C8.2, C9.2, C10.2, J1.3, J1.4, J1.5, J2.3, J2.4, J2.5, Q1.2 (S), R1.2, R2.2, R3.2, R7.2, U1.2 (AGND), U1.6 (PGND)
unnamed: C3.1, R4.2

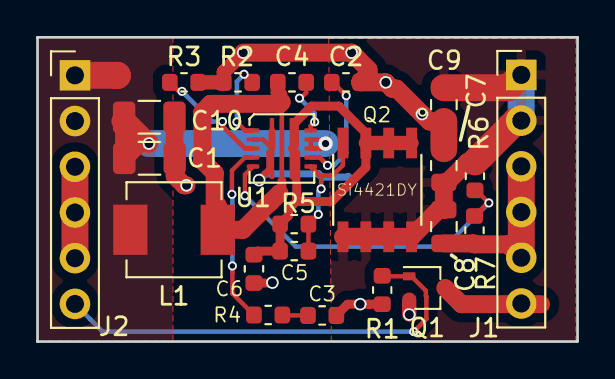
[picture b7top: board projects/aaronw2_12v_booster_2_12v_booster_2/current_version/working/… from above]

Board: 2 copper layers, 30.0 x 16.9 mm, 23 parts (0 on the bottom side), 15 nets.
